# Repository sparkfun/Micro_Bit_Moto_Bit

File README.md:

SparkFun moto:bit
========================================

[*SparkFun moto:bit (DEV-14213)*](https://www.sparkfun.com/products/14213)

The SparkFun moto:bit is a fully loaded “carrier” board for the micro:bit that, when combined with the micro:bit, provides you with a fully functional robotics platform. The moto:bit offers a simple, beginner-friendly robotics controller capable of operating a basic robotics chassis. Onboard each moto:bit are multiple I/O pins capable of hooking up servos, sensors and other circuits. At the flip of the switch you can get your micro:bit moving!

Repository Contents
-------------------

* **/Firmware** - Example code used in the micro:bot Kit Experiment Guide and Wireless Remote Control with micro:bit tutorials. While they are compiled HEX codes, you can modify the example code once they are imported into MakeCode editor.
* **/Hardware** - Eagle design files (.brd, .sch)
* **/Production** - Production panel files (.brd)

Documentation
--------------
* **[Library](https://github.com/sparkfun/pxt-moto-bit)** - PXT gamer:bit firmware
* **[micro:bot Kit Experiment Guide](https://learn.sparkfun.com/tutorials/microbot-kit-experiment-guide/)** - Experiment guide using the moto:bit carrier board.
* **[Wireless Remote Control with micro:bit](https://learn.sparkfun.com/tutorials/wireless-remote-control-with-microbit)** - Project guide using the micro:bot and micro:arcade kits. By utilizing the radio blocks, you can wirelessly control the micro:bot using the gamer:bit.

License Information
-------------------

This product is _**open source**_! 

Please review the LICENSE.md file for license information. 

If you have any questions or concerns on licensing, please contact techsupport@sparkfun.com.

Distributed as-is; no warranty is given.

- Your friends at SparkFun.

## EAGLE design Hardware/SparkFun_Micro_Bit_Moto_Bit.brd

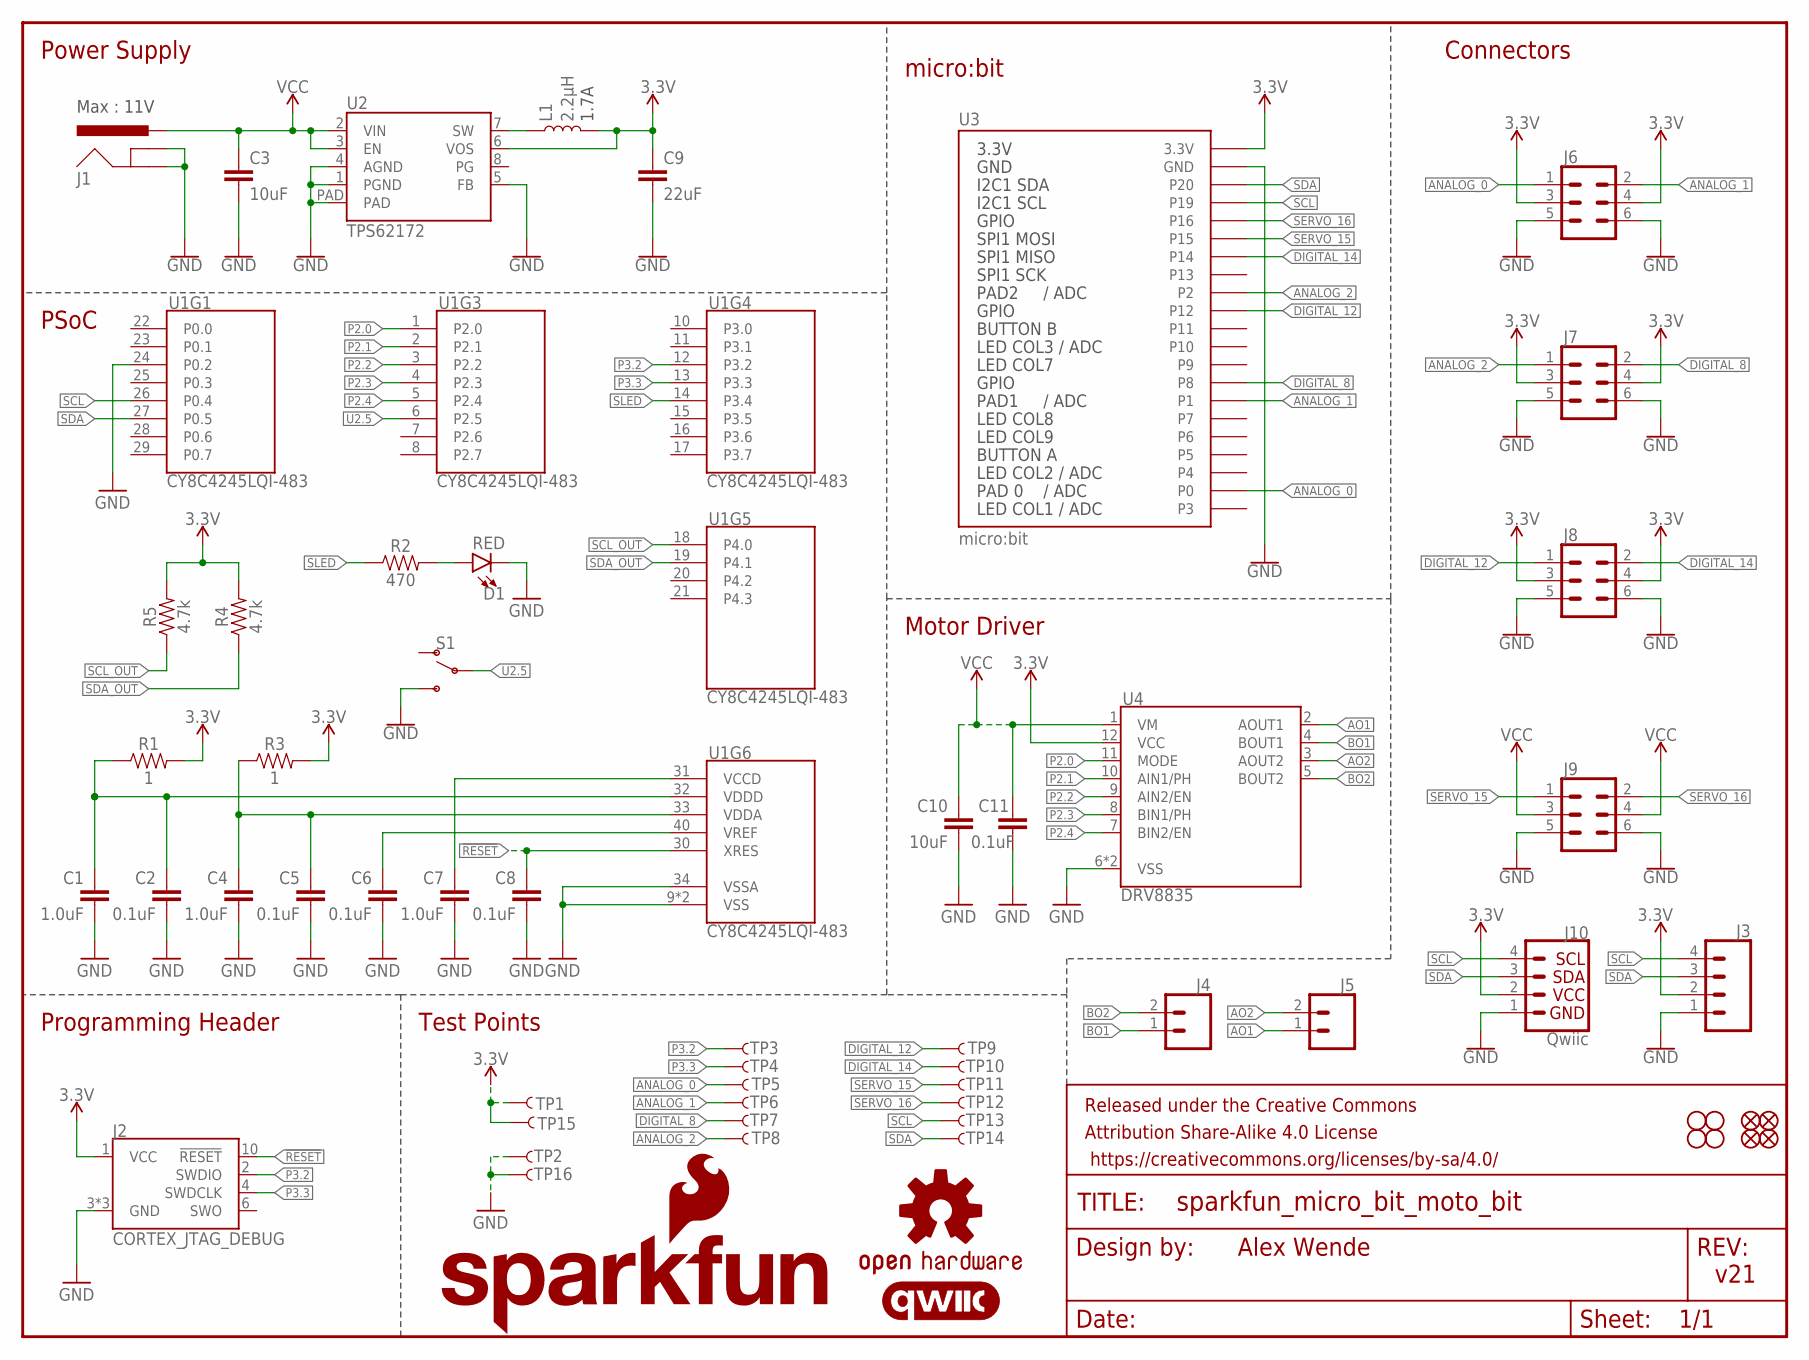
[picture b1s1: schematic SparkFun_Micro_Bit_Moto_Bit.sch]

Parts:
C1, C4, C7: 1.0uF; 0603
C2, C5, C6, C8, C11: 0.1uF; 0603
C3, C10: 10uF; 1210
C9: 22uF; 0805
D1: RED; LED-0603
FD1, FD2, FD3, FD4: FIDUCIALUFIDUCIAL; FIDUCIAL-MICRO
FRAME1: FRAME-LETTER; CREATIVE_COMMONS
H1, H2, H3, H4: STAND-OFF
J1: POWER_JACKPTH_LOCK; POWER_JACK_PTH_LOCK
J2: CORTEX_JTAG_DEBUG; 2X5-PTH-1.27MM-NO_SILK
J3: CONN_04SMD_STRAIGHT_COMBO; 1X04_SMD_VERTICAL_COMBO
J4, J5: CONN_02PTH_RA_FEMALE; 1X02_RA_PTH_FEMALE
J6, J7, J8, J9: CONN_03X2SMT; 2X3_SMT_POSTS
J10: Qwiic; JST04_1MM_VERT
L1: 2.2μH; 0805-WIDE
LOGO1: SFE_LOGO_NAME_FLAME.3_INCH; SFE_LOGO_NAME_FLAME_.3
LOGO2: OSHW-LOGOL; OSHW-LOGO-L
LOGO3: QWIIC_LOGO_5MM; QWIIC_5MM
R1, R3: 1; 0603
R2: 470; 0603
R4, R5: 4.7k; 0603
S1: SWITCH-SPDT-PTH-8.6X4.3MM-LOCK; SWITCH_SPDT_8.6X4.3MM_LOCK
TP1, TP2, TP3, TP4, TP5, TP6, TP7, TP8, TP9, TP10, TP11, TP12, TP13, TP14, TP15, TP16: TEST-POINT3; PAD.03X.03
U1: CY8C4245LQI-483; QFN-40
U2: TPS62172; WSON-8-PAD
U3: micro:bit; MICRO:BIT-RA_SMD
U4: DRV8835; WSON-12

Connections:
3.3V: C9.1, J2.1 (VCC), J3.2, J6.3, J6.4, J7.3, J7.4, J8.3, J8.4, J10.2, L1.2, R1.2, R3.2, R4.2, R5.2, TP1.P$1, TP15.P$1, U2.6 (VOS), U3.P$27 (3.3V), U3.P$28 (3.3V), U3.P$29 (3.3V), U3.P$30 (3.3V), U3.P$31 (3.3V), U3.P$32 (3.3V), U4.12 (VCC)
!RESET: C8.1, J2.10 (!RESET), U1.30 (XRES)
ANALOG_0: J6.1, TP5.P$1, U3.P$2 (P0), U3.P$3 (P0), U3.P$4 (P0), U3.P$5 (P0)
ANALOG_1: J6.2, TP6.P$1, U3.P$10 (P1), U3.P$11 (P1), U3.P$12 (P1), U3.P$13 (P1)
ANALOG_2: J7.1, TP8.P$1, U3.P$19 (P2), U3.P$20 (P2), U3.P$21 (P2), U3.P$22 (P2)
AO1: J5.1, U4.2 (AOUT1)
AO2: J5.2, U4.3 (AOUT2)
BO1: J4.1, U4.4 (BOUT1)
BO2: J4.2, U4.5 (BOUT2)
DIGITAL_8: J7.2, TP7.P$1, U3.P$14 (P8)
DIGITAL_12: J8.1, TP9.P$1, U3.P$18 (P12)
DIGITAL_14: J8.2, TP10.P$1, U3.P$24 (P14)
GND: C1.2, C2.2, C3.2, C4.2, C5.2, C6.2, C7.2, C8.2, C9.2, C10.2, C11.2, D1.C, J1.GND, J1.GNDBREAK, J2.3 (GND), J2.5 (GND), J2.9 (GND), J3.1, J6.5, J6.6, J7.5, J7.6, J8.5, J8.6, J9.5, J9.6, J10.1, S1.3 (S), TP2.P$1, TP16.P$1, U1.9 (VSS), U1.24 (P0.2), U1.34 (VSSA), U1.EP (VSS), U2.1 (PGND), U2.4 (AGND), U2.5 (FB), U2.PAD, U3.P$35 (GND), U3.P$36 (GND), U3.P$37 (GND), U3.P$38 (GND), U3.P$39 (GND), U3.P$40 (GND), U4.6 (VSS), U4.PAD (VSS)
unnamed: C7.1, U1.31 (VCCD)
unnamed: C6.1, U1.40 (VREF)
unnamed: C4.1, C5.1, R3.1, U1.33 (VDDA)
unnamed: L1.1, U2.7 (SW)
unnamed: D1.A, R2.2
P2.0: U1.1 (P2.0), U4.11 (MODE)
P2.1: U1.2 (P2.1), U4.10 (AIN1/PH)
P2.2: U1.3 (P2.2), U4.9 (AIN2/EN)
P2.3: U1.4 (P2.3), U4.8 (BIN1/PH)
P2.4: U1.5 (P2.4), U4.7 (BIN2/EN)
P3.2: J2.2 (SWDIO), TP3.P$1, U1.12 (P3.2)
P3.3: J2.4 (SWDCLK), TP4.P$1, U1.13 (P3.3)
SCL: J3.4, J10.4, TP13.P$1, U1.26 (P0.4), U3.P$33 (P19)
SCL_OUT: R5.1, U1.18 (P4.0)
SDA: J3.3, J10.3, TP14.P$1, U1.27 (P0.5), U3.P$34 (P20)
SDA_OUT: R4.1, U1.19 (P4.1)
SERVO_15: J9.1, TP11.P$1, U3.P$25 (P15)
SERVO_16: J9.2, TP12.P$1, U3.P$26 (P16)
SLED: R2.1, U1.14 (P3.4)
U2.5: S1.2, U1.6 (P2.5)
VCC: C3.1, C10.1, C11.1, J1.PWR, J9.3, J9.4, U2.2 (VIN), U2.3 (EN), U4.1 (VM)
VDDD: C1.1, C2.1, R1.1, U1.32 (VDDD)

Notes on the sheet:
1.7A
Power Supply
Motor Driver
Connectors
micro:bit
Alex Wende
v21
PSoC
Programming Header
Max : 11V
Test Points

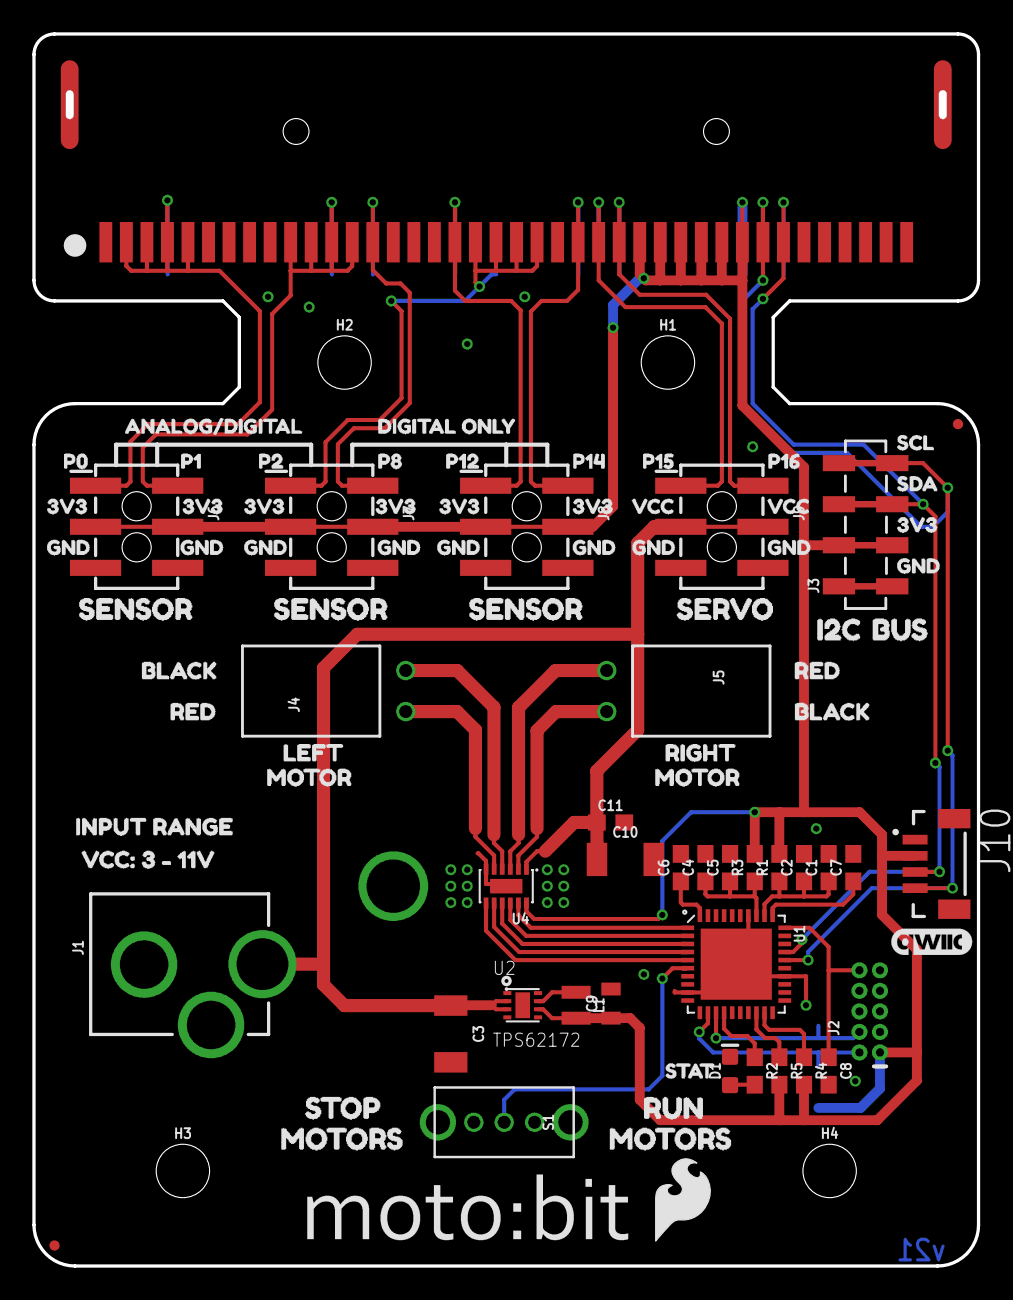
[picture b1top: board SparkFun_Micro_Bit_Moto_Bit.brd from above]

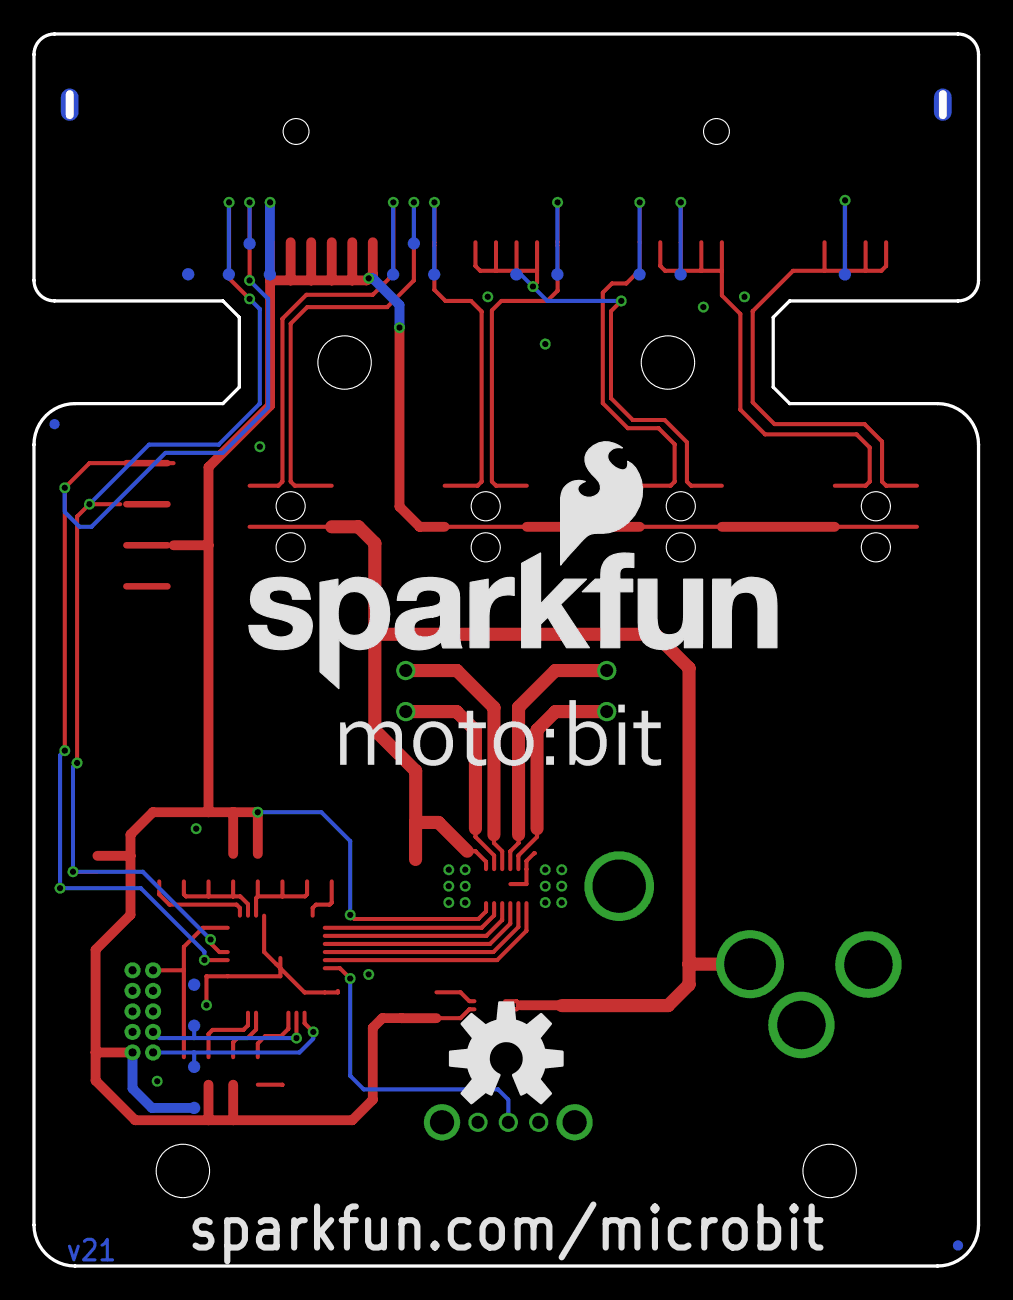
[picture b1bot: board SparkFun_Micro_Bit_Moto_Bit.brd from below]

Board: 2 copper layers, 58.1 x 75.9 mm, 116 parts (21 on the bottom side), 35 nets.

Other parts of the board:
U$1: PRODUCTION_INSTRUCTIONS
U$2: SFE_LOGO_FLAME_.2
U$3, U$4: LOGO-MOTOBIT
U$5, U$9, U$12, U$15, U$18, U$21, U$31: 3V31
U$6, U$10, U$13, U$16, U$19, U$22, U$25, U$28, U$32: GND0
U$7: P02
U$8: P13
U$11: P24
U$14: P85
U$17: P126
U$20: P147
U$23: P158
U$24, U$27: VCC10
U$26: P169
U$29: SCL2
U$30: SDA3
U$33: I2C4
U$34: BUS5
U$35: SERVO6
U$36, U$37, U$38: SENSOR7
U$39: ANALOG#DIGITAL0
U$40: DIGITAL_ONLY1
U$41, U$44: BLACK8
U$42, U$43: RED9
U$45: LEFT10
U$46, U$48: MOTOR11
U$47: RIGHT12
U$49: INPUT_RANGE13
U$50: VCC#_3_#_11V14
U$51: STOP15
U$52, U$54: MOTORS16
U$53: RUN17
U$55: STAT18

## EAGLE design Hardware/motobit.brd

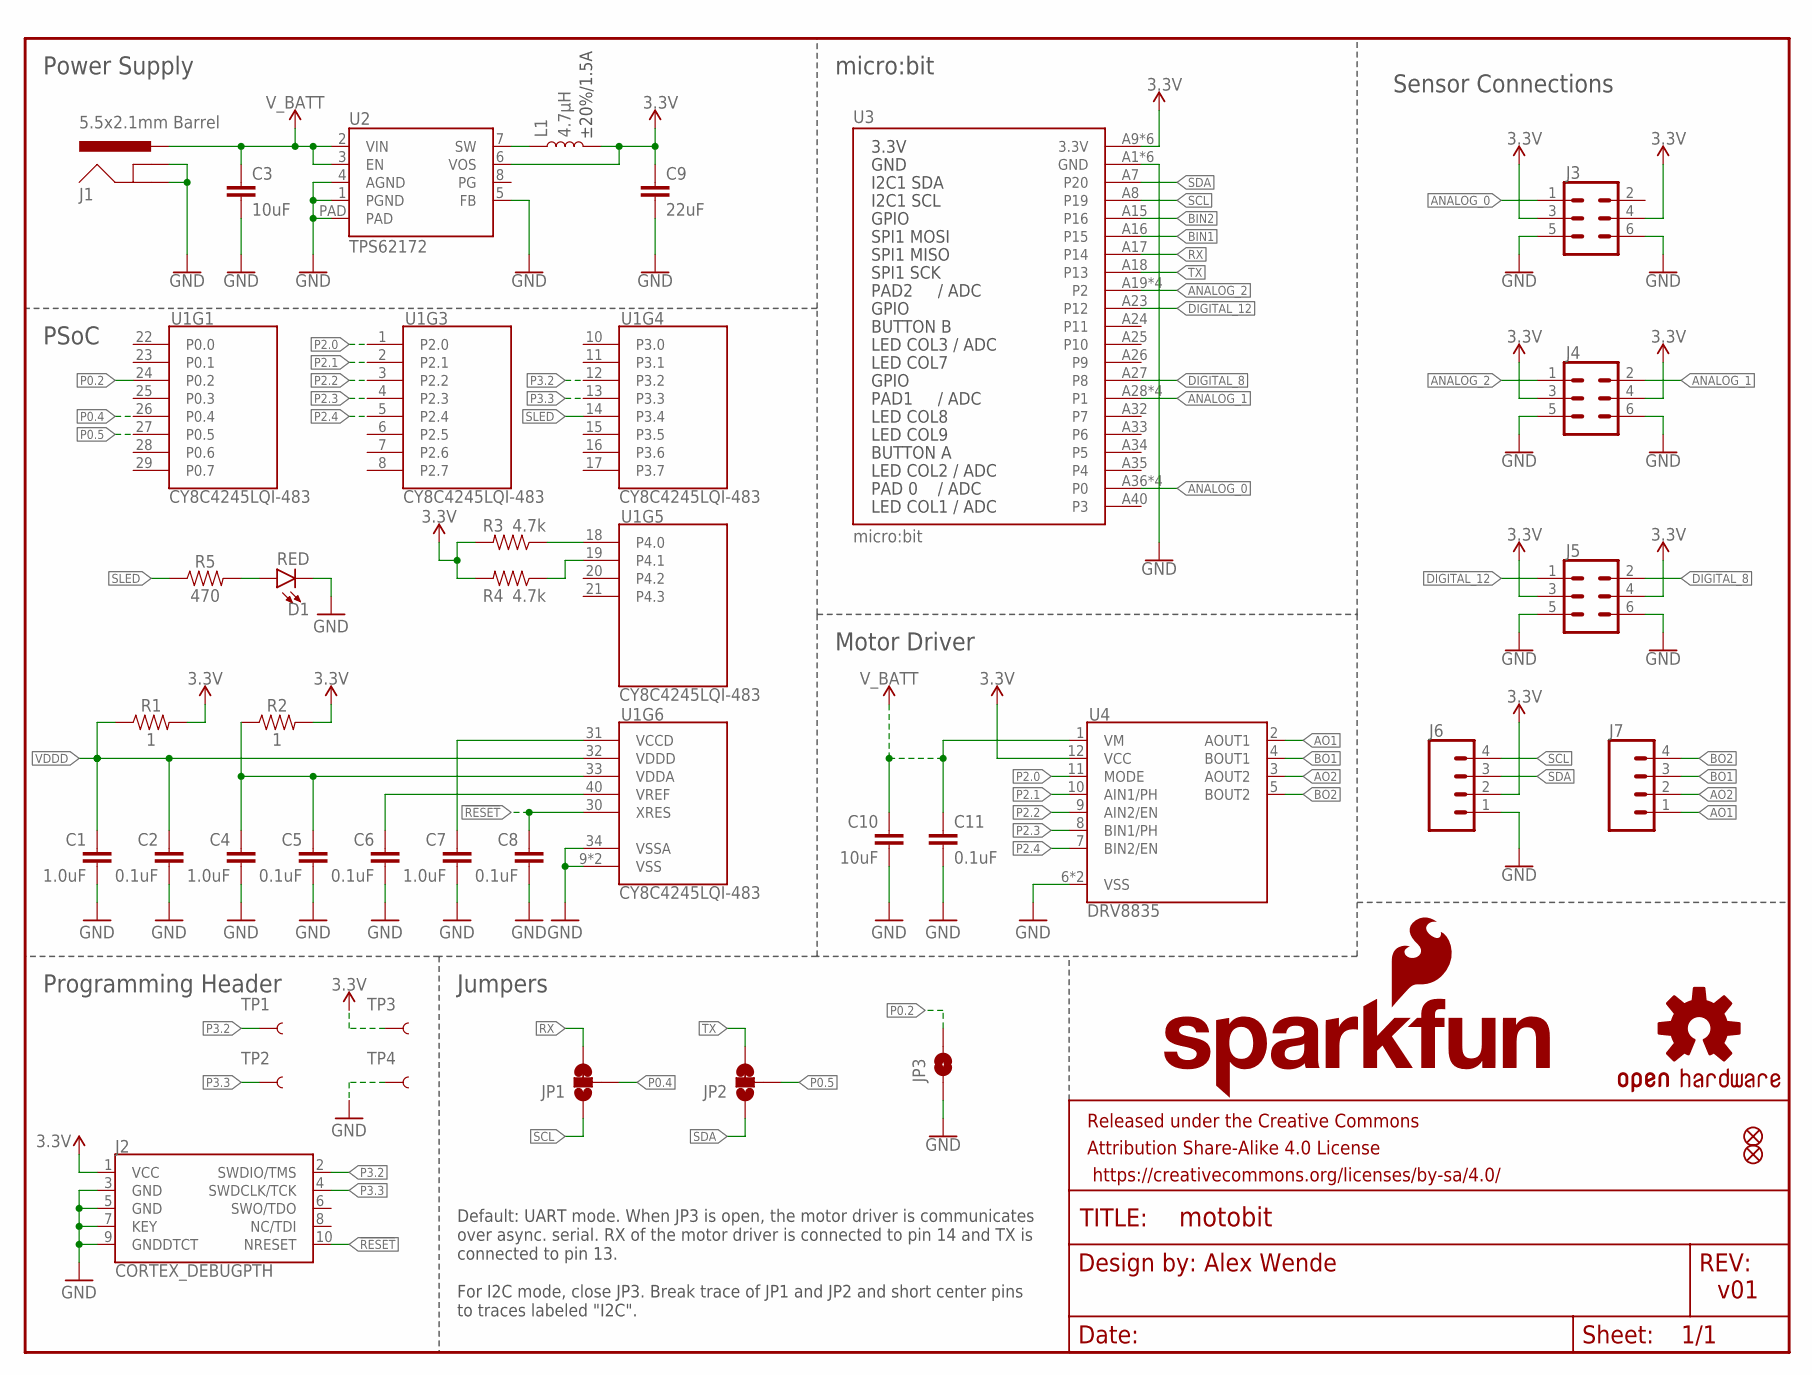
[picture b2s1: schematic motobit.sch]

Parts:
C1, C4, C7: 1.0uF; 0603
C2, C5, C6, C8, C11: 0.1uF; 0603
C3, C10: 10uF; 1210
C9: 22uF; 0805
D1: RED; LED-0603
FD1, FD2: FIDUCIALUFIDUCIAL; FIDUCIAL-MICRO
FRAME1: FRAME-LETTER; CREATIVE_COMMONS
J1: 5.5x2.1mm Barrel; POWER_JACK_SMD
J2: CORTEX_DEBUGPTH; 2X5-PTH-1.27MM
J3, J4, J5: CONN_03X2FEMALE_SMD; 2X3_SMD
J6: CONN_04SMD_STRAIGHT_COMBO; 1X04_SMD_VERTICAL_COMBO
J7: CONN_04SMD_RA_FEMALE; 1X04_SMD_RA_FEMALE
JP1, JP2: JUMPER-SMT_3_1-NC_TRACE_SILK; SMT-JUMPER_3_1-NC_TRACE_SILK
JP3: JUMPER-SMT_2_NO_SILK; SMT-JUMPER_2_NO_SILK
L1: 4.7µH; INDUCTOR_2.2UH
LOGO1: SFE_LOGO_NAME_FLAME.2_INCH; SFE_LOGO_NAME_FLAME_.2
LOGO2: OSHW-LOGOM; OSHW-LOGO-M
R1, R2: 1; 0603
R3, R4: 4.7k; 0603
R5: 470; 0603
TP1, TP2, TP3, TP4: TEST-POINT3; PAD.03X.03
U1: CY8C4245LQI-483; QFN-40
U2: TPS62172; WSON-8-PAD
U3: micro:bit; MICRO:BIT_RA_PTH
U4: DRV8835; WSON-12

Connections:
3.3V: C9.1, J2.1 (VCC), J3.3, J3.4, J4.3, J4.4, J5.3, J5.4, J6.2, L1.P$2 (2), R1.2, R2.2, R3.2, R4.2, TP3.P$1, U2.6 (VOS), U3.A9 (3.3V), U3.A10 (3.3V), U3.A11 (3.3V), U3.A12 (3.3V), U3.A13 (3.3V), U3.A14 (3.3V), U4.12 (VCC)
!RESET: C8.1, J2.10 (NRESET), U1.30 (XRES)
ANALOG_0: J3.1, U3.A36 (P0), U3.A37 (P0), U3.A38 (P0), U3.A39 (P0)
ANALOG_1: J4.2, U3.A28 (P1), U3.A29 (P1), U3.A30 (P1), U3.A31 (P1)
ANALOG_2: J4.1, U3.A19 (P2), U3.A20 (P2), U3.A21 (P2), U3.A22 (P2)
AO1: J7.1, U4.2 (AOUT1)
AO2: J7.2, U4.3 (AOUT2)
BIN1: U3.A16 (P15)
BIN2: U3.A15 (P16)
BO1: J7.3, U4.4 (BOUT1)
BO2: J7.4, U4.5 (BOUT2)
DIGITAL_8: J5.2, U3.A27 (P8)
DIGITAL_12: J5.1, U3.A23 (P12)
GND: C1.2, C2.2, C3.2, C4.2, C5.2, C6.2, C7.2, C8.2, C9.2, C10.2, C11.2, D1.C, J1.GND (GNDBREAK), J1.P$4 (GND), J2.3 (GND), J2.5 (GND), J2.7 (KEY), J2.9 (GNDDTCT), J3.5, J3.6, J4.5, J4.6, J5.5, J5.6, J6.1, JP3.1, TP4.P$1, U1.9 (VSS), U1.34 (VSSA), U1.EP (VSS), U2.1 (PGND), U2.4 (AGND), U2.5 (FB), U2.PAD, U3.A1 (GND), U3.A2 (GND), U3.A3 (GND), U3.A4 (GND), U3.A5 (GND), U3.A6 (GND), U4.6 (VSS), U4.PAD (VSS)
unnamed: C7.1, U1.31 (VCCD)
unnamed: C6.1, U1.40 (VREF)
unnamed: C4.1, C5.1, R2.1, U1.33 (VDDA)
unnamed: L1.P$1 (1), U2.7 (SW)
unnamed: R3.1, U1.18 (P4.0)
unnamed: R4.1, U1.19 (P4.1)
unnamed: D1.A, R5.2
P0.2: JP3.2, U1.24 (P0.2)
P0.4: JP1.2, U1.26 (P0.4)
P0.5: JP2.2, U1.27 (P0.5)
P2.0: U1.1 (P2.0), U4.11 (MODE)
P2.1: U1.2 (P2.1), U4.10 (AIN1/PH)
P2.2: U1.3 (P2.2), U4.9 (AIN2/EN)
P2.3: U1.4 (P2.3), U4.8 (BIN1/PH)
P2.4: U1.5 (P2.4), U4.7 (BIN2/EN)
P3.2: J2.2 (SWDIO/TMS), TP1.P$1, U1.12 (P3.2)
P3.3: J2.4 (SWDCLK/TCK), TP2.P$1, U1.13 (P3.3)
RX: JP1.3, U3.A17 (P14)
SCL: J6.4, JP1.1, U3.A8 (P19)
SDA: J6.3, JP2.1, U3.A7 (P20)
SLED: R5.1, U1.14 (P3.4)
TX: JP2.3, U3.A18 (P13)
VDDD: C1.1, C2.1, R1.1, U1.32 (VDDD)
V_BATT: C3.1, C10.1, C11.1, J1.VIN0 (PWR), U2.2 (VIN), U2.3 (EN), U4.1 (VM)

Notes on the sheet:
±20%/1.5A
Power Supply
Motor Driver
Sensor Connections
micro:bit
Alex Wende
v01
PSoC
Programming Header
Jumpers
Default: UART mode. When JP3 is open, the motor driver is communicates over async. serial. RX of the motor driver is connected to pin 14 and TX is connected to pin 13. For I2C mode, close JP3. Break trace of JP1 and JP2 and short center pins to traces labeled "I2C".

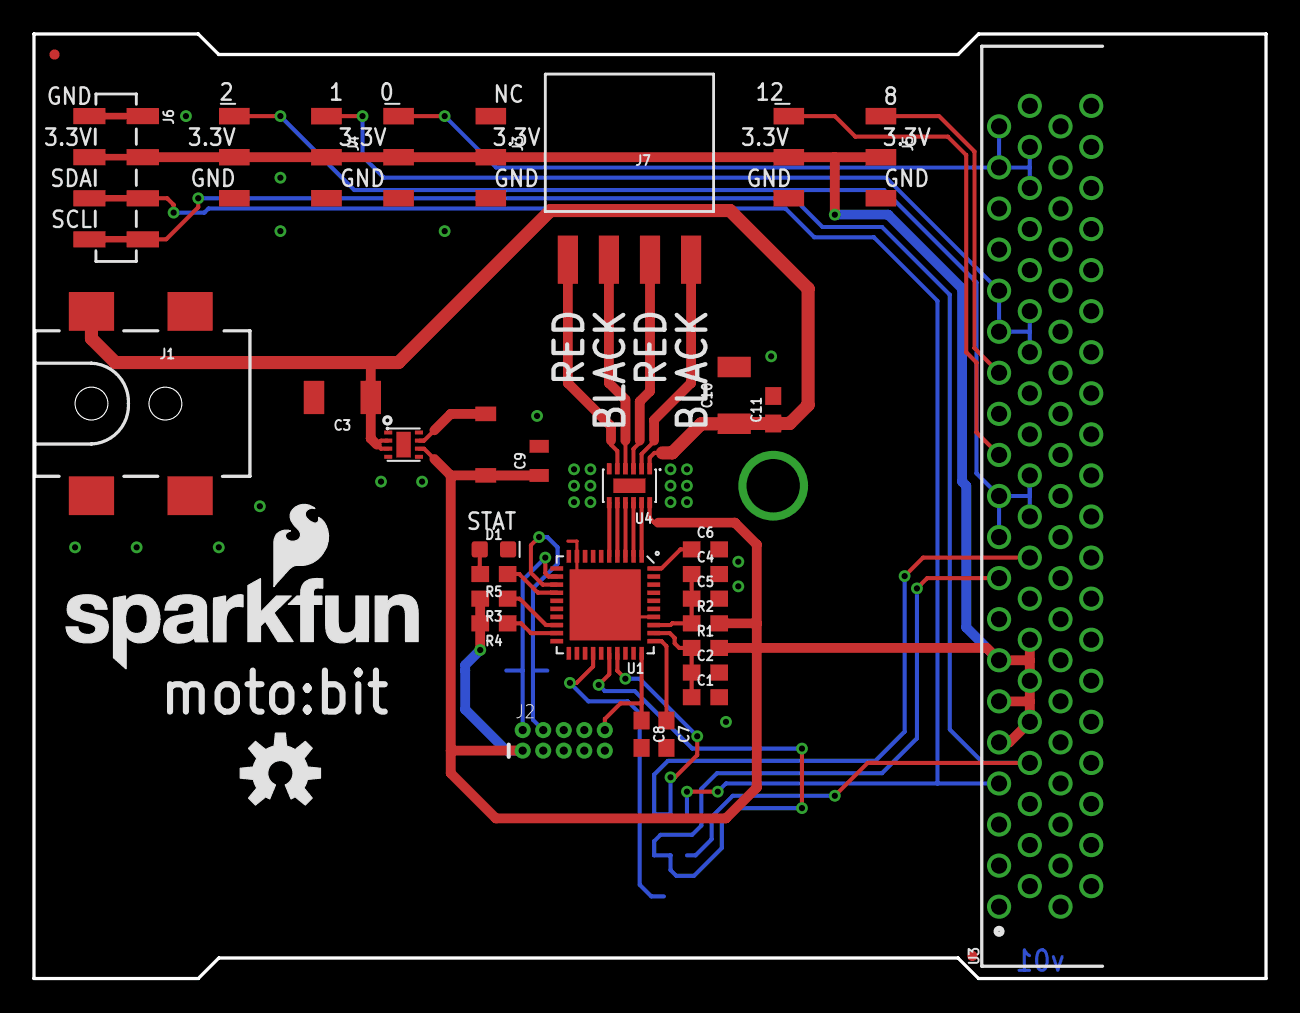
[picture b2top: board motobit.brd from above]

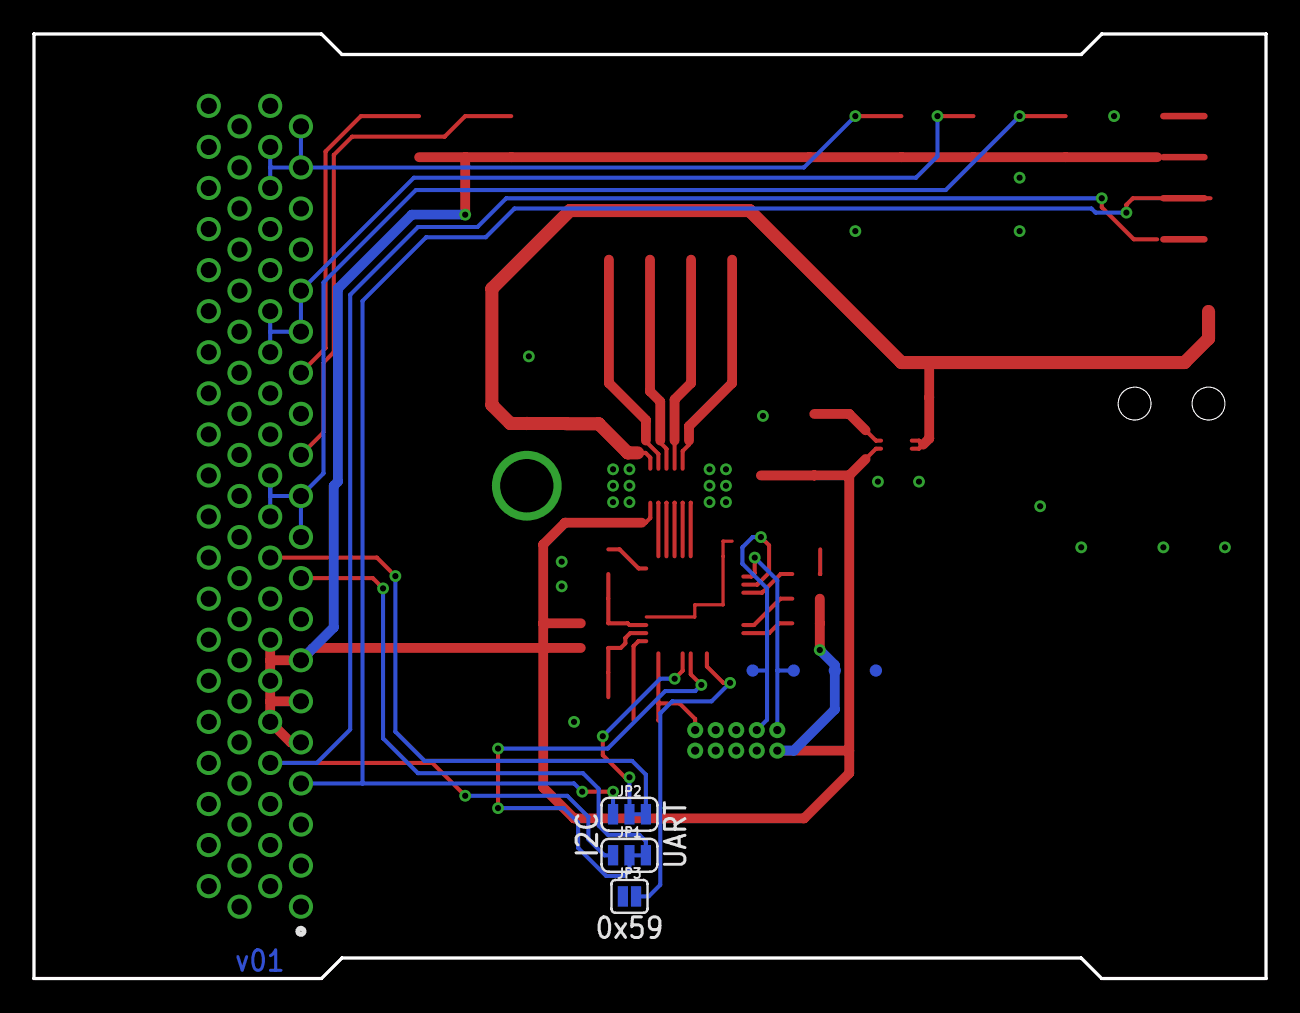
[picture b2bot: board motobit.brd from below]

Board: 2 copper layers, 76.2 x 58.4 mm, 42 parts (7 on the bottom side), 36 nets.

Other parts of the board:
U$1: PRODUCTION_INSTRUCTIONS

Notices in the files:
parts and their libraries:
SparkFun-Aesthetics: Licensing: Creative Commons ShareAlike 4.0 International - https://creativecommons.org/licenses/by-sa/4.0
SparkFun-Aesthetics: Released under the Creative Commons Attribution Share-Alike 4.0 License
SparkFun-Aesthetics: https://creativecommons.org/licenses/by-sa/4.0
